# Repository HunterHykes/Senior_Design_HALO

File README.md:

# Senior_Design_HALO

This is the repository for the Hard Hat Ambient Liability Observer (H.A.L.O.) I assisted in developing for my senior design project at the University of Akron from Spring 2020 - Spring 2021.

<p align="center">

<p align="center">H.A.L.O. attached to a hard hat.</p>
</p>

<p align="center">

<p align="center">H.A.L.O. detached from a hard hat.</p>
</p>

## What the H.A.L.O. Does
This product is a hard hat attachment which utilizes six time-of-flight (ToF) sensors to detect hazards within a 1.5m radius from the wearer's head with a 150° field of view.

<p align="center">

<p align="center">H.A.L.O. Time-of-Flight Board.</p>
</p>

Dependent on the distance between the user and the hazard, some RGB LEDs placed near the brim of the hard hat will turn on and change hue from yellow to red as objects approach. This enhances the awareness of the user of potential hazards.

<p align="center">

<p align="center">H.A.L.O. RGB LED Board.</p>
</p>

In the event that the user hits their head either from a collision from walking or perhaps from slipping and falling, an on-board accelerometer will detect the impact severity.

If this impact is determined to pose a concussion threat to the user, the accelerometer data is logged to a .csv file on a micro-SD card, which can then be used to assess health-related concerns.

## Images

<p align="center">

<p align="center">H.A.L.O. being worn by myself.</p>
</p>

<!---  --->
<!---  --->
<!---  --->
<!---  --->
<!---  --->

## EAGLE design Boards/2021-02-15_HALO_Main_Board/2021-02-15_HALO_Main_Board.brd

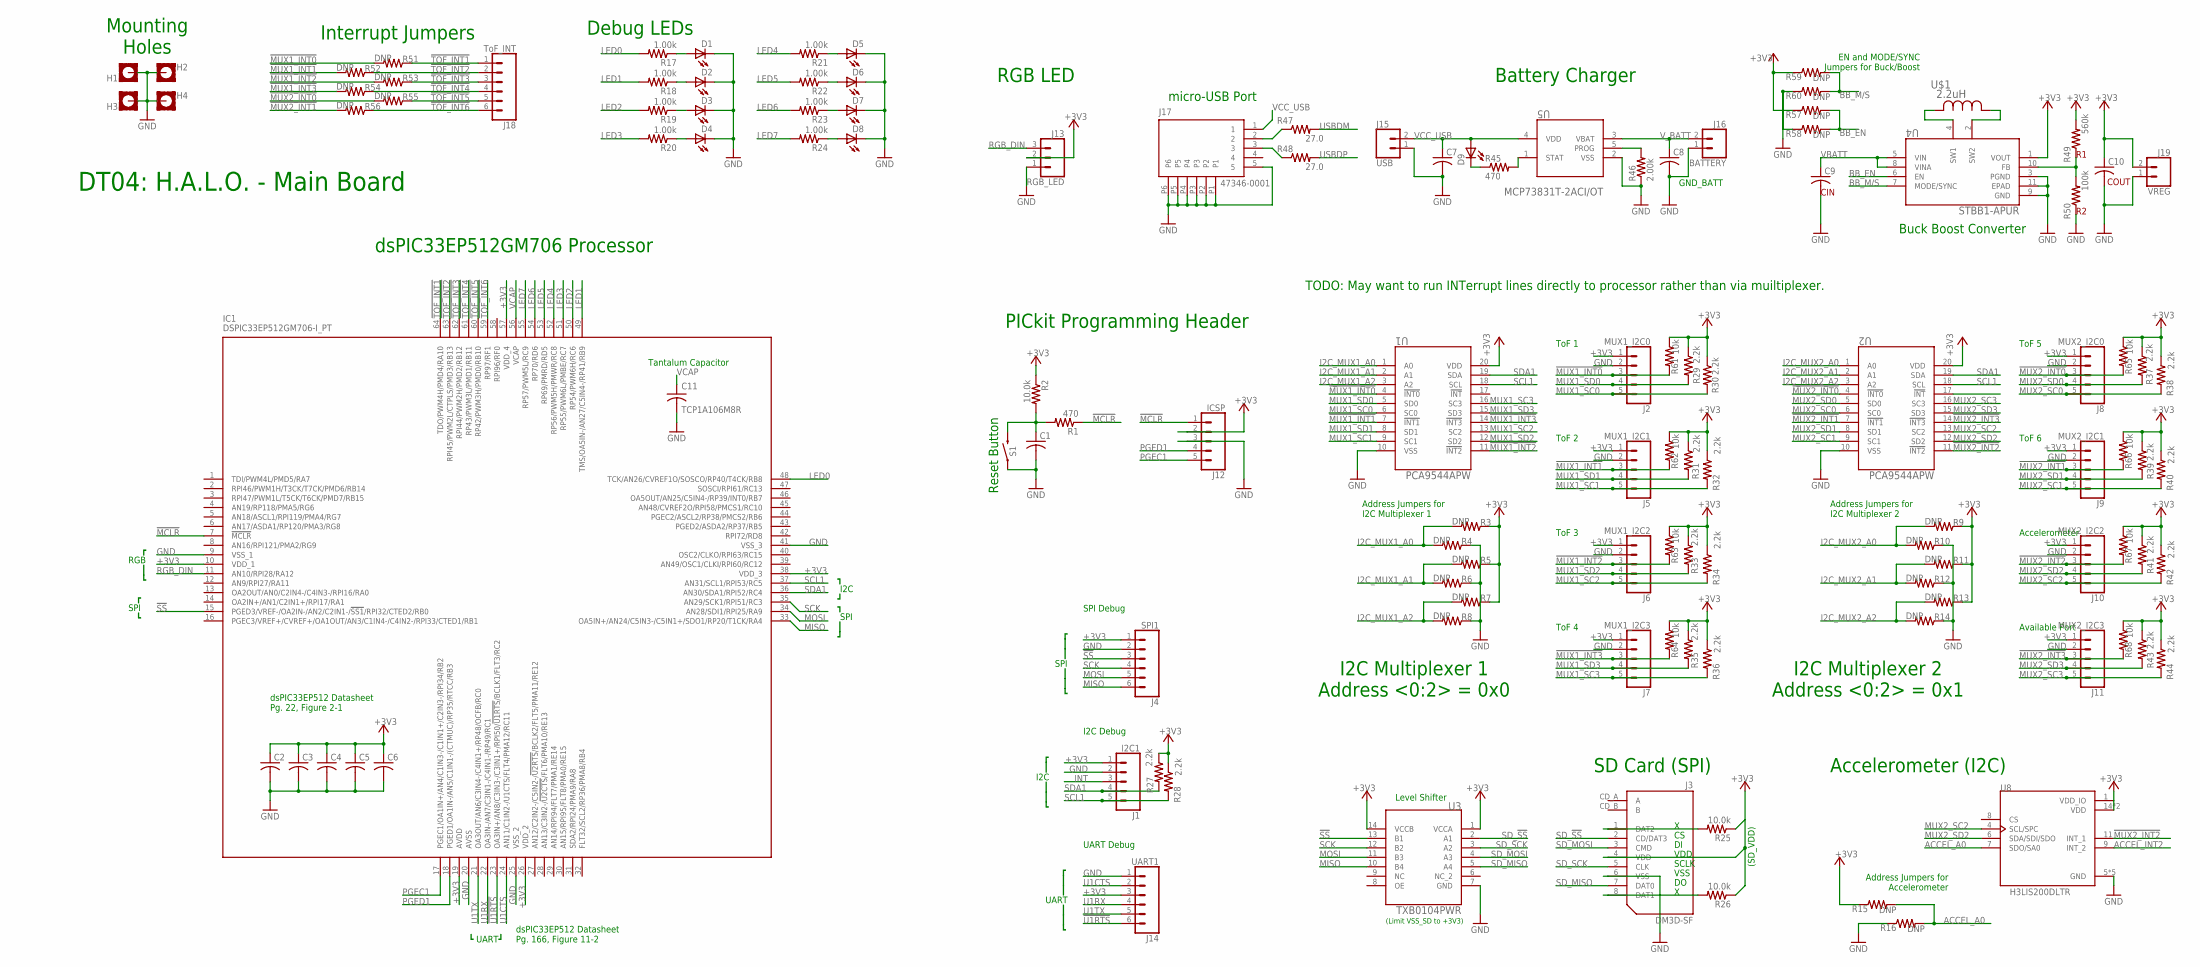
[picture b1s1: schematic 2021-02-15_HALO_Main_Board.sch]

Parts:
C1, C2, C3, C4, C5, C6: 0.1uF; C0805
C7, C8: 4.7uF; C0805
C9: 10uF; C0805
C10: 22uF; C0805
C11: TCP1A106M8R; TCP_ROM
D1, D2, D3, D4, D5, D6, D7, D8, D9: CHIP-LED0805
H1, H2, H3, H4: MOUNT-PAD-SQUARE3.0; 3,0-PAD-SQUARE
IC1: DSPIC33EP512GM706-I_PT; QFP50P1200X1200X120-64N
J1: I2C1; 1X05
J2: MUX1_I2C0; 1X05
J3: DM3D-SF; SD_CARD
J4: SPI1; 1X06
J5: MUX1_I2C1; 1X05
J6: MUX1_I2C2; 1X05
J7: MUX1_I2C3; 1X05
J8: MUX2_I2C0; 1X05
J9: MUX2_I2C1; 1X05
J10: MUX2_I2C2; 1X05
J11: MUX2_I2C3; 1X05
J12: ICSP; 1X05
J13: RGB_LED; 1X03_LOCK
J14: UART1; 1X06
J15: USB; 1X02
J16: BATTERY; 1X02
J17: 47346-0001; MICRO_USB; PARTNO AS-ITM-00021
J18: ToF_INT; 1X06
J19: VREG; 1X02
R1, R45: 470; R0805
R2, R25, R26: 10.0k; R0805
R3, R4, R5, R6, R7, R8, R9, R10, R11, R12, R13, R14, R15, R16, R51, R52, R53, R54, R55, R56, R57, R58, R59, R60: DNP; R0805
R17, R18, R19, R20, R21, R22, R23, R24: 1.00k; R0805
R27, R28, R29, R30, R31, R32, R33, R34, R35, R36, R37, R38, R39, R40, R41, R42, R43, R44: 2.2k; R0805
R46: 2.00k; R0805
R47, R48: 27.0; R0805
R49: 560k; R0805
R50: 100k; R0805
R61, R62, R63, R64, R65, R66, R67, R68: 10k; R0805
S1: SWITCH-MOMENTARY-2SMD-4; TACTILE_SWITCH_TALL
U1, U2: PCA9544APW; SOT360-1_NXP
U3: TXB0104PWR; PW14
U4: STBB1-APUR; SON_B1-APUR_STM
U5: MCP73831T-2ACI/OT; SOT-23-5_MC_MCH
U8: H3LIS200DLTR; PQFN50P300X300X100-16N
U$1: 2.2uH; IND_4028_TDK

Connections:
!MCLR: IC1.7 (!MCLR), J12.1, R1.1
!MUX1_INT0: J2.3, R51.2, R61.2, U1.4 (!INT0)
!MUX1_INT1: J5.3, R52.2, R62.2, U1.7 (!INT1)
!MUX1_INT2: J6.3, R53.2, R63.2, U1.11 (!INT2)
!MUX1_INT3: J7.3, R54.2, R64.2, U1.14 (!INT3)
!MUX2_INT0: J8.3, R55.2, R65.2, U2.4 (!INT0)
!MUX2_INT1: J9.3, R56.2, R66.2, U2.7 (!INT1)
!MUX2_INT2: J10.3, R67.2, U2.11 (!INT2), U8.11 (INT_1)
!MUX2_INT3: J11.3, R68.2, U2.14 (!INT3)
!SS: IC1.15 (PGED3/VREF-/OA2IN-/AN2/C2IN1-/!SS1!/RPI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), J4.3, U3.13 (B1)
!TOF_INT1: IC1.64 (TDO/PWM4H/PMD4/RA10), J18.1, R51.1
!TOF_INT2: IC1.63 (RPI45/PWM2L/CTPLS/PMD3/RB13), J18.2, R52.1
!TOF_INT3: IC1.62 (RPI44/PWM2H/PMD2/RB12), J18.3, R53.1
!TOF_INT4: IC1.61 (RP43/PWM3L/PMD1/RB11), J18.4, R54.1
!TOF_INT5: IC1.60 (RP42/PWM3H/PMD0/RB10), J18.5, R55.1
!TOF_INT6: IC1.59 (RP97/RF1), J18.6, R56.1
!U1RTS: IC1.23 (OA3IN+/AN8/C3IN3-/C3IN1+/RPI50/!U1RTS!/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), J14.6
+3V3: C2.1, C3.1, C4.1, C5.1, C6.1, C10.1, IC1.10 (VDD_1), IC1.19 (AVDD), IC1.26 (VDD_2), IC1.38 (VDD_3), IC1.57 (VDD_4), J1.1, J2.1, J3.4 (VDD), J4.1, J5.1, J6.1, J7.1, J8.1, J9.1, J10.1, J11.1, J12.2, J13.2, J14.3, J19.2, R2.1, R3.1, R5.1, R7.1, R9.1, R11.1, R13.1, R15.1, R25.1, R26.1, R27.1, R28.1, R29.1, R30.1, R31.1, R32.1, R33.1, R34.1, R35.1, R36.1, R37.1, R38.1, R39.1, R40.1, R41.1, R42.1, R43.1, R44.1, R49.2, R57.1, R59.1, R61.1, R62.1, R63.1, R64.1, R65.1, R66.1, R67.1, R68.1, U1.20 (VDD), U2.20 (VDD), U3.1 (VCCA), U3.14 (VCCB), U4.1 (VOUT), U8.1 (VDD_IO), U8.14 (VDD), U8.15 (VDD)
ACCEL_A0: R15.2, R16.2, U8.7 (SDO/SA0)
ACCEL_INT2: U8.9 (INT_2)
BB_EN: R57.2, R58.2, U4.6 (EN)
BB_M/S: R59.2, R60.2, U4.7 (MODE/SYNC)
GND: C1.2, C2.2, C3.2, C4.2, C5.2, C6.2, C7.2, C8.2, C9.2, C10.2, C11.2, D1.C, D2.C, D3.C, D4.C, D5.C, D6.C, D7.C, D8.C, H1.B3,0, H2.B3,0, H3.B3,0, H4.B3,0, IC1.9 (VSS_1), IC1.20 (AVSS), IC1.25 (VSS_2), IC1.41 (VSS_3), J1.2, J2.2, J3.6 (VSS), J4.2, J5.2, J6.2, J7.2, J8.2, J9.2, J10.2, J11.2, J12.3, J13.1, J14.1, J15.1, J16.1, J17.5, J17.P1, J17.P2, J17.P3, J17.P4, J17.P5, J17.P6, J19.1, R4.1, R6.1, R8.1, R10.1, R12.1, R14.1, R16.1, R46.1, R50.1, R58.1, R60.1, S1.A2 (1), U1.10 (VSS), U2.10 (VSS), U3.7 (GND), U4.3 (PGND), U4.9 (GND), U4.11 (EPAD), U5.2 (VSS), U8.5 (GND), U8.10 (GND), U8.12 (GND), U8.13 (GND), U8.16 (GND)
I2C_MUX1_A0: R3.2, R4.2, U1.1 (A0)
I2C_MUX1_A1: R5.2, R6.2, U1.2 (A1)
I2C_MUX1_A2: R7.2, R8.2, U1.3 (A2)
I2C_MUX2_A0: R9.2, R10.2, U2.1 (A0)
I2C_MUX2_A1: R11.2, R12.2, U2.2 (A1)
I2C_MUX2_A2: R13.2, R14.2, U2.3 (A2)
INT: J1.3
LED0: IC1.48 (TCK/AN26/CVREF1O/SOSCO/RP40/T4CK/RB8), R17.2
LED1: IC1.49 (TMS/OA5IN-/AN27/C5IN4-/RP41/RB9), R18.2
LED2: IC1.50 (RP54/PWM6H/RC6), R19.2
LED3: IC1.51 (RP55/PWM6L/PMBE/RC7), R20.2
LED4: IC1.52 (RP56/PWM5H/PMWR/RC8), R21.2
LED5: IC1.53 (RP69/PMRD/RD5), R22.2
LED6: IC1.54 (RP70/RD6), R23.2
LED7: IC1.55 (RP57/PWM5L/RC9), R24.2
MISO: IC1.33 (OA5IN+/AN24/C5IN3-/C5IN1+/SDO1/RP20/T1C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), J4.6, U3.10 (B4)
MOSI: IC1.34 (AN28/SDI1/RPI25/RA9), J4.5, U3.11 (B3)
MUX1_SC0: J2.5, R30.2, U1.6 (SC0)
MUX1_SC1: J5.5, R32.2, U1.9 (SC1)
MUX1_SC2: J6.5, R34.2, U1.13 (SC2)
MUX1_SC3: J7.5, R36.2, U1.16 (SC3)
MUX1_SD0: J2.4, R29.2, U1.5 (SD0)
MUX1_SD1: J5.4, R31.2, U1.8 (SD1)
MUX1_SD2: J6.4, R33.2, U1.12 (SD2)
MUX1_SD3: J7.4, R35.2, U1.15 (SD3)
MUX2_SC0: J8.5, R38.2, U2.6 (SC0)
MUX2_SC1: J9.5, R40.2, U2.9 (SC1)
MUX2_SC2: J10.5, R42.2, U2.13 (SC2), U8.4 (SCL/SPC)
MUX2_SC3: J11.5, R44.2, U2.16 (SC3)
MUX2_SD0: J8.4, R37.2, U2.5 (SD0)
MUX2_SD1: J9.4, R39.2, U2.8 (SD1)
MUX2_SD2: J10.4, R41.2, U2.12 (SD2), U8.6 (SDA/SDI/SDO)
MUX2_SD3: J11.4, R43.2, U2.15 (SD3)
unnamed: C1.1, R1.2, R2.2, S1.B2 (2)
unnamed: J3.8 (DAT1), R26.2
unnamed: J3.1 (DAT2), R25.2
unnamed: D1.A, R17.1
unnamed: J17.2, R47.1
unnamed: D2.A, R18.1
unnamed: D9.C, R45.1
unnamed: R49.1, R50.2, U4.10 (FB)
unnamed: D3.A, R19.1
unnamed: D4.A, R20.1
unnamed: D5.A, R21.1
unnamed: D6.A, R22.1
unnamed: D7.A, R23.1
unnamed: D8.A, R24.1
unnamed: R45.2, U5.1 (STAT)
unnamed: J17.3, R48.1
unnamed: U4.4 (SW1), U$1.2
unnamed: R46.2, U5.5 (PROG)
unnamed: U4.2 (SW2), U$1.1
PGEC1: IC1.17 (PGEC1/OA1IN+/AN4/C1IN3-/C1IN1+/C2IN3-/R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), J12.5
PGED1: IC1.18 (PGED1/OA1IN-/AN5/C1IN1-/(CTMUC)/RP35/RT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), J12.4
RGB_DIN: IC1.11 (AN10/RPI28/RA12), J13.3
SCK: IC1.35 (AN29/SCK1/RPI51/RC3), J4.4, U3.12 (B2)
SCL1: IC1.37 (AN31/SCL1/RPI53/RC5), J1.5, R28.2, U1.18 (SCL), U2.18 (SCL)
SDA1: IC1.36 (AN30/SDA1/RPI52/RC4), J1.4, R27.2, U1.19 (SDA), U2.19 (SDA)
SD_!SS: J3.2 (CD/DAT3), U3.2 (A1)
SD_MISO: J3.7 (DAT0), U3.5 (A4)
SD_MOSI: J3.3 (CMD), U3.4 (A3)
SD_SCK: J3.5 (CLK), U3.3 (A2)
U1CTS: IC1.24 (AN11/C1IN2-/U1CTS/FLT4/PMA12/RC11), J14.2
U1RX: IC1.22 (OA3IN-/AN7/C3IN1-/C4IN1-/RP49/RC1), J14.4
U1TX: IC1.21 (OA3OUT/AN6/C3IN4-/C4IN1+/RP48/OCFB/RC0), J14.5
USBDM: R47.2
USBDP: R48.2
VBATT: C9.1, U4.5 (VIN), U4.8 (VINA)
VCAP: C11.1, IC1.56 (VCAP)
VCC_USB: C7.1, D9.A, J15.2, J17.1, U5.4 (VDD)
V_BATT: C8.1, J16.2, U5.3 (VBAT)

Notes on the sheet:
┓ SPI ┃ ┛
┓ I2C ┛
Reset Button
VDD
SCLK
VSS
SD Card (SPI)
Address Jumpers for I2C Multiplexer 1
Address Jumpers for I2C Multiplexer 2
I2C Debug
SPI Debug
I2C Multiplexer 1 Address <0:2> = 0x0
I2C Multiplexer 2 Address <0:2> = 0x1
ToF 1
ToF 2
ToF 3
ToF 4
ToF 5
ToF 6
Accelerometer
Available Port
TODO: May want to run INTerrupt lines directly to processor rather than via muiltiplexer.
DT04: H.A.L.O. - Main Board
dsPIC33EP512 Datasheet Pg. 22, Figure 2-1
PICkit Programming Header
Debug LEDs
dsPIC33EP512 Datasheet Pg. 166, Figure 11-2
┗ UART┛
Level Shifter
(Limit VSS_SD to +3V3)
(SD_VDD)
RGB LED
Battery Charger
Buck Boost Converter
GND_BATT
Accelerometer (I2C)
Address Jumpers for Accelerometer
UART Debug
┏ ┃ I2C ┃ ┃ ┗
┏ ┃ ┃ SPI ┃ ┃ ┗

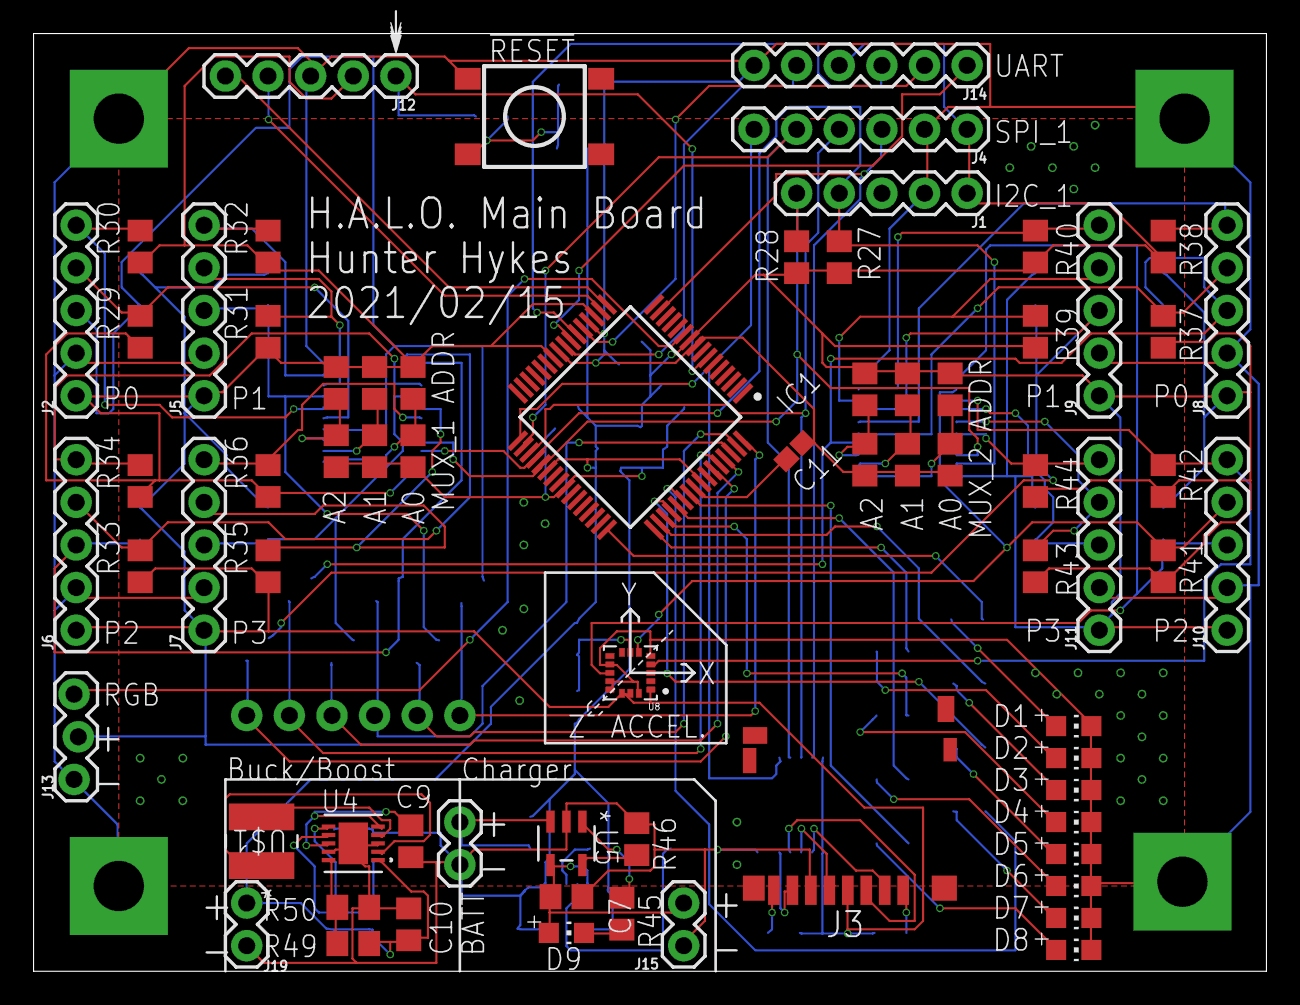
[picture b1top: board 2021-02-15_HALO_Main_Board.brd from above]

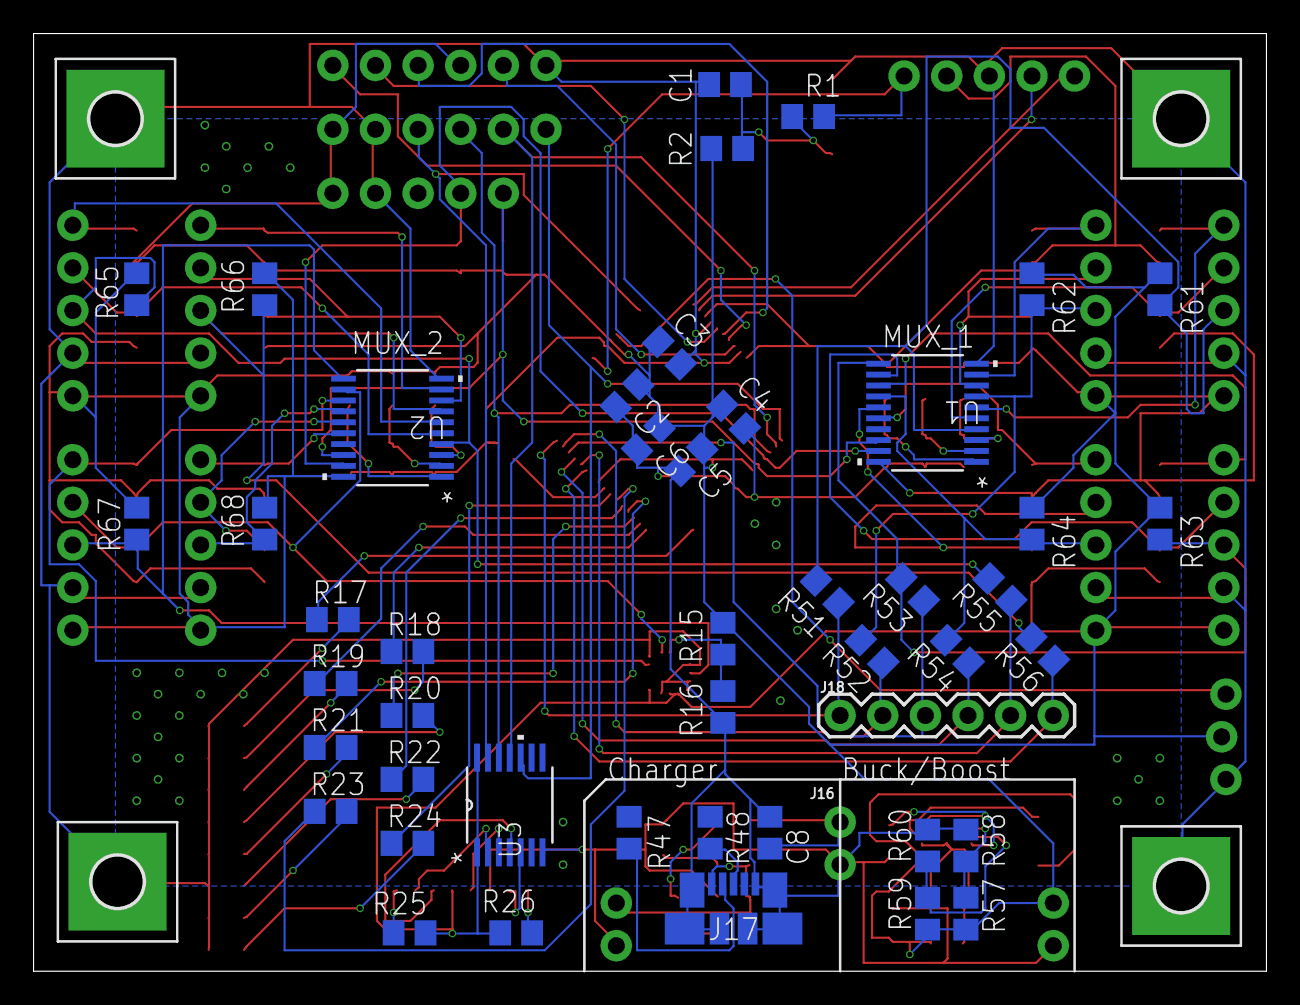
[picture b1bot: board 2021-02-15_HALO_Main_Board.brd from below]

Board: 2 copper layers, 73.5 x 55.9 mm, 120 parts (50 on the bottom side), 90 nets.

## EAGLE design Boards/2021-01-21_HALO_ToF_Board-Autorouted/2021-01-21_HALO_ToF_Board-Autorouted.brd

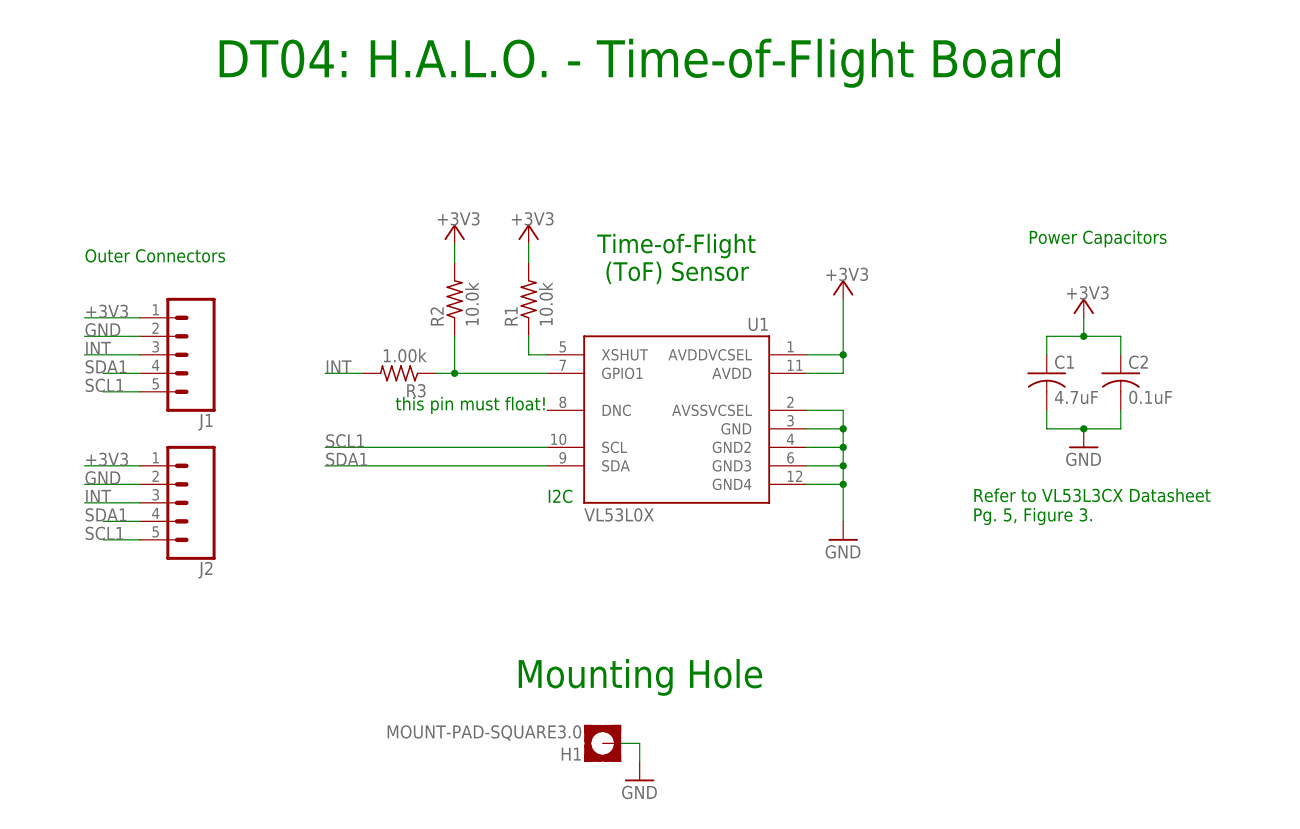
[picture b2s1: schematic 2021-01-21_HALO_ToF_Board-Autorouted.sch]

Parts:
C1: 4.7uF; C0805
C2: 0.1uF; C0805
H1: MOUNT-PAD-SQUARE3.0; 3,0-PAD-SQUARE
J1, J2: CONN_05; 1X05
R1, R2: 10.0k; R0805
R3: 1.00k; R0805
U1: VL53L0X

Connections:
+3V3: C1.1, C2.1, J1.1, J2.1, R1.2, R2.2, U1.1 (AVDDVCSEL), U1.11 (AVDD)
GND: C1.2, C2.2, H1.B3,0, J1.2, J2.2, U1.2 (AVSSVCSEL), U1.3 (GND), U1.4 (GND2), U1.6 (GND3), U1.12 (GND4)
INT: J1.3, J2.3, R3.2
unnamed: R1.1, U1.5 (XSHUT)
unnamed: R2.1, R3.1, U1.7 (GPIO1)
SCL1: J1.5, J2.5, U1.10 (SCL)
SDA1: J1.4, J2.4, U1.9 (SDA)

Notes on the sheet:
Outer Connectors
Refer to VL53L3CX Datasheet Pg. 5, Figure 3.
Power Capacitors
Time-of-Flight (ToF) Sensor
I2C
this pin must float!
DT04: H.A.L.O. - Time-of-Flight Board
Mounting Hole

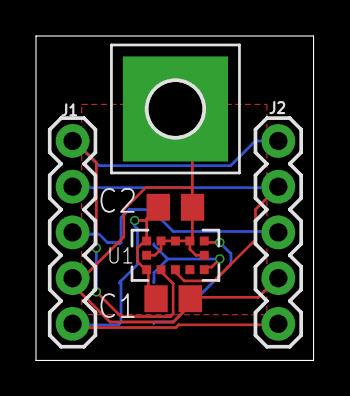
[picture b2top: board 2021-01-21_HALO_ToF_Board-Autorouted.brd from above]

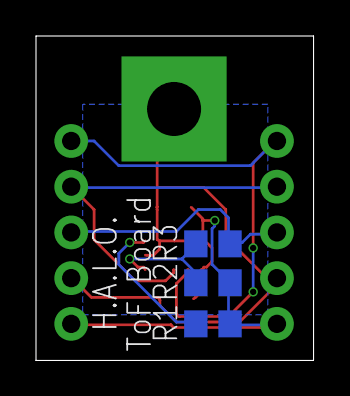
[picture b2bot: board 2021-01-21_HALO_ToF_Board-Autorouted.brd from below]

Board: 2 copper layers, 15.4 x 18.0 mm, 9 parts (3 on the bottom side), 7 nets.

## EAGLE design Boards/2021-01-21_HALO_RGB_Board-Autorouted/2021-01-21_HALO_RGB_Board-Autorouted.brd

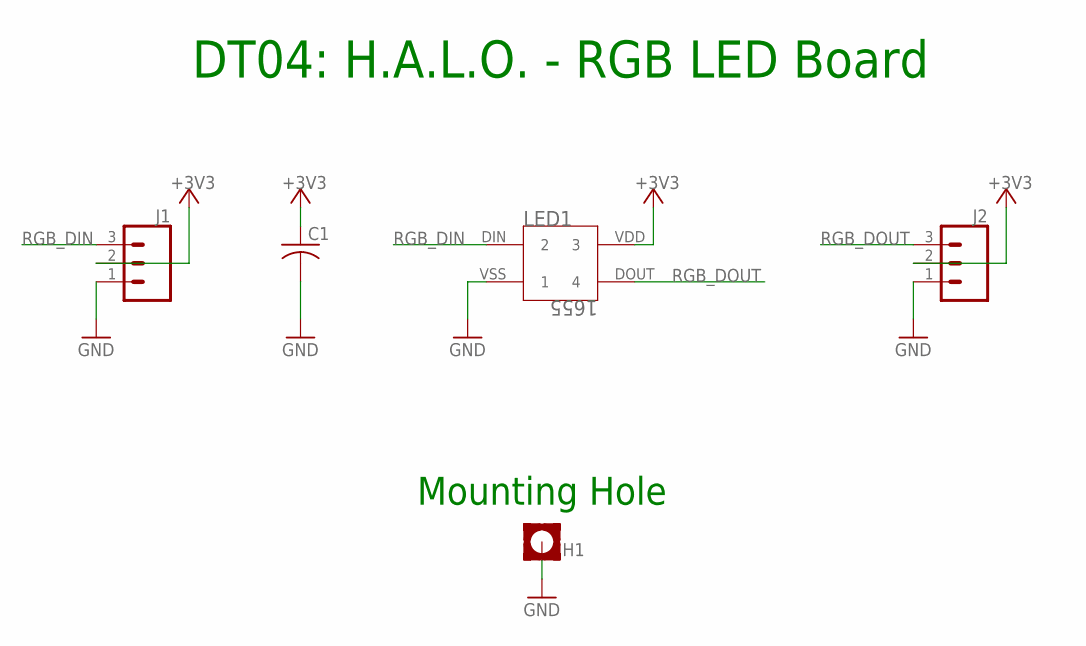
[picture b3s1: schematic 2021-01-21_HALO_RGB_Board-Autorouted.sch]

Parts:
C1: 1uF; C0805
H1: MOUNT-PAD-SQUARE3.0; 3,0-PAD-SQUARE
J1, J2: CONN_03LOCK; 1X03_LOCK
LED1: 1655; LED_1655_ADA

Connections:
+3V3: C1.1, J1.2, J2.2, LED1.VDD (3)
GND: C1.2, H1.B3,0, J1.1, J2.1, LED1.VSS (1)
RGB_DIN: J1.3, LED1.DIN (2)
RGB_DOUT: J2.3, LED1.DOUT (4)

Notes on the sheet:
DT04: H.A.L.O. - RGB LED Board
Mounting Hole

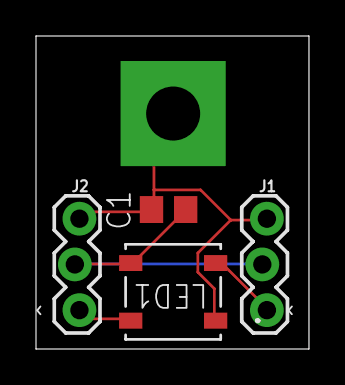
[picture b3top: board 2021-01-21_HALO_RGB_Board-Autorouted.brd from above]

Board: 2 copper layers, 15.2 x 17.4 mm, 5 parts (1 on the bottom side), 4 nets.

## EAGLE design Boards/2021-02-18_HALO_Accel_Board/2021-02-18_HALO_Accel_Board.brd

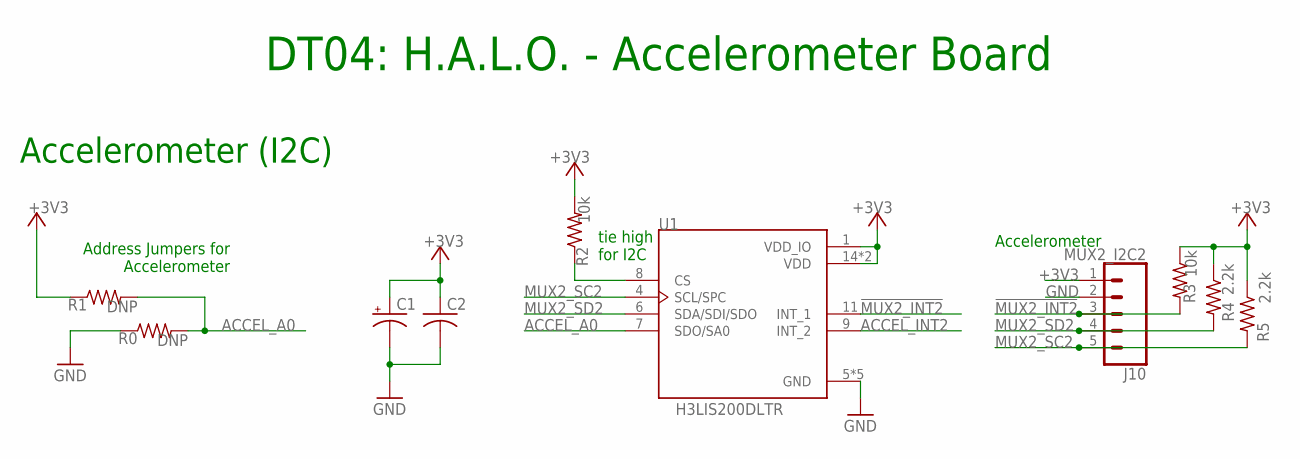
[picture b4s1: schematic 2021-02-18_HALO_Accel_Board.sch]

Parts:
C1: 10uF; EIA3216
C2: 0.1uF; C0805
J10: MUX2_I2C2; 1X05
R0, R1: DNP; R0805
R2, R3: 10k; R0805
R4, R5: 2.2k; R0805
U1: H3LIS200DLTR; PQFN50P300X300X100-16N

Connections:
!MUX2_INT2: J10.3, R3.2, U1.11 (INT_1)
+3V3: C1.+, C2.1, J10.1, R1.1, R2.2, R3.1, R4.1, R5.1, U1.1 (VDD_IO), U1.14 (VDD), U1.15 (VDD)
ACCEL_A0: R0.2, R1.2, U1.7 (SDO/SA0)
ACCEL_INT2: U1.9 (INT_2)
GND: C1.-, C2.2, J10.2, R0.1, U1.5 (GND), U1.10 (GND), U1.12 (GND), U1.13 (GND), U1.16 (GND)
MUX2_SC2: J10.5, R5.2, U1.4 (SCL/SPC)
MUX2_SD2: J10.4, R4.2, U1.6 (SDA/SDI/SDO)
unnamed: R2.1, U1.8 (CS)

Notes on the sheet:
Accelerometer
DT04: H.A.L.O. - Accelerometer Board
Accelerometer (I2C)
Address Jumpers for Accelerometer
tie high for I2C

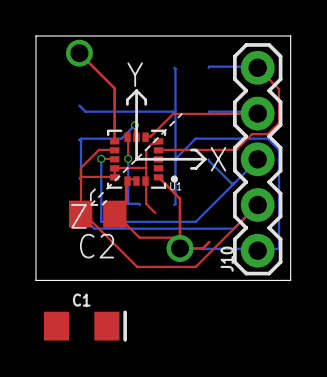
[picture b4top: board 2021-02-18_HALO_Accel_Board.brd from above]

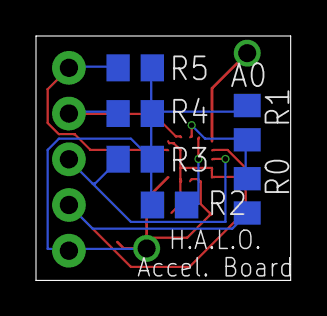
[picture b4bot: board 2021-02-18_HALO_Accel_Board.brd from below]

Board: 2 copper layers, 14.1 x 13.6 mm, 10 parts (6 on the bottom side), 7 nets.

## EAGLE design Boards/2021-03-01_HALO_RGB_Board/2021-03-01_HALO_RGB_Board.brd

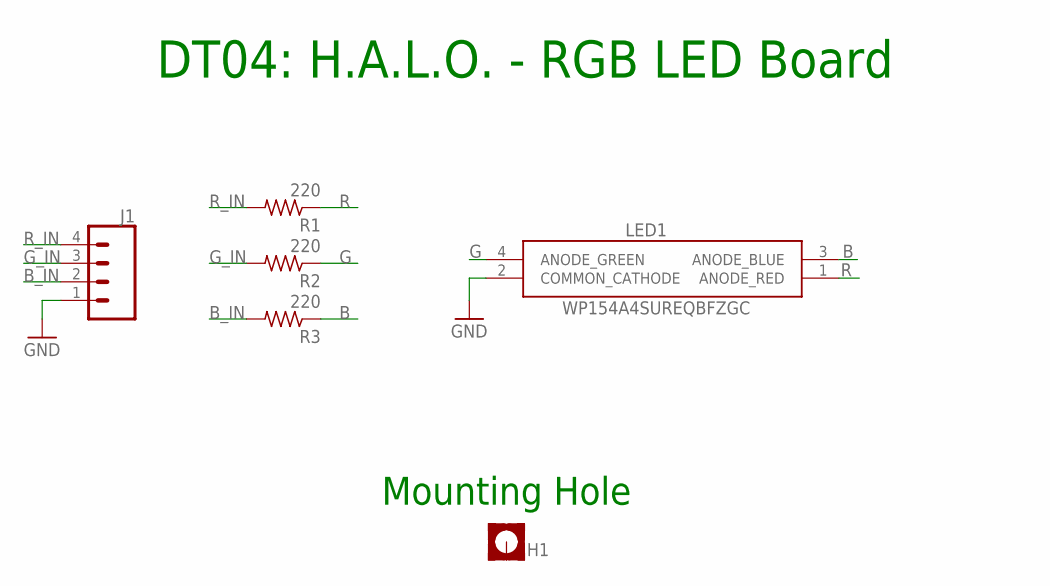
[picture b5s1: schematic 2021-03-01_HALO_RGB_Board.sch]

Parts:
H1: MOUNT-PAD-SQUARE3.0; 3,0-PAD-SQUARE
J1: CONN_04; 1X04
LED1: WP154A4SUREQBFZGC; L-154A4SUREQBFZGEC
R1, R2, R3: 220; R0805

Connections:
B: LED1.3 (ANODE_BLUE), R3.1
B_IN: J1.2, R3.2
G: LED1.4 (ANODE_GREEN), R2.1
GND: J1.1, LED1.2 (COMMON_CATHODE)
G_IN: J1.3, R2.2
R: LED1.1 (ANODE_RED), R1.1
R_IN: J1.4, R1.2

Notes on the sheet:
DT04: H.A.L.O. - RGB LED Board
Mounting Hole

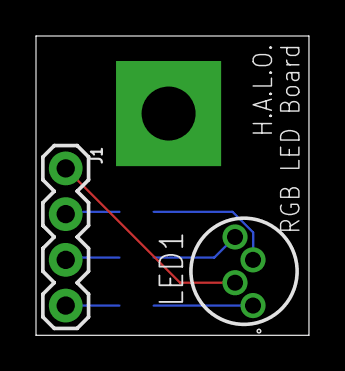
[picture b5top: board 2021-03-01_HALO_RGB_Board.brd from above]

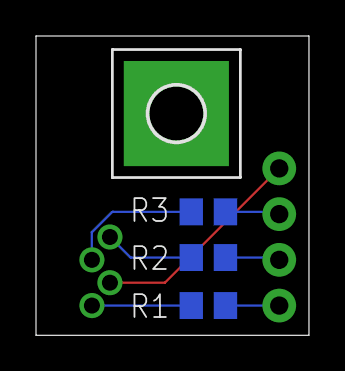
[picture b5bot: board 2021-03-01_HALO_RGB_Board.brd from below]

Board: 2 copper layers, 15.2 x 16.6 mm, 6 parts (4 on the bottom side), 7 nets.

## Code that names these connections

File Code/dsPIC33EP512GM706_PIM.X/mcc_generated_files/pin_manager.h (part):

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*/
/**
  @Summary
    Sets the GPIO pin, RA10, high using LATA10.

  @Description
    Sets the GPIO pin, RA10, high using LATA10.

  @Preconditions
    The RA10 must be set to an output.
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#define ToF_INT1_SetHigh()          (_LATA10 = 1)
/**
  @Summary
    Sets the GPIO pin, RA10, low using LATA10.

  @Description
    Sets the GPIO pin, RA10, low using LATA10.

  @Preconditions
    The RA10 must be set to an output.
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#define ToF_INT1_SetLow()           (_LATA10 = 0)
/**
  @Summary
    Toggles the GPIO pin, RA10, using LATA10.

  @Description
    Toggles the GPIO pin, RA10, using LATA10.

  @Preconditions
    The RA10 must be set to an output.
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#define ToF_INT1_Toggle()           (_LATA10 ^= 1)
/**
  @Summary
    Reads the value of the GPIO pin, RA10.

  @Description
    Reads the value of the GPIO pin, RA10.

  @Preconditions
    None.
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    </code>

*/
#define ToF_INT1_GetValue()         _RA10
/**
  @Summary
    Configures the GPIO pin, RA10, as an input.

  @Description
    Configures the GPIO pin, RA10, as an input.

  @Preconditions
    None.
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#define ToF_INT1_SetDigitalInput()  (_TRISA10 = 1)
/**
  @Summary
    Configures the GPIO pin, RA10, as an output.

  @Description
    Configures the GPIO pin, RA10, as an output.

  @Preconditions
    None.
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#define ToF_INT1_SetDigitalOutput() (_TRISA10 = 0)
/**
  @Summary
    Sets the GPIO pin, RA4, high using LATA4.

  @Description
    Sets the GPIO pin, RA4, high using LATA4.

  @Preconditions
    The RA4 must be set to an output.
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#define SDO1_SetHigh()          (_LATA4 = 1)
/**
  @Summary
    Sets the GPIO pin, RA4, low using LATA4.

  @Description
    Sets the GPIO pin, RA4, low using LATA4.

  @Preconditions
    The RA4 must be set to an output.
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#define SDO1_SetLow()           (_LATA4 = 0)
/**
  @Summary
    Toggles the GPIO pin, RA4, using LATA4.

  @Description
    Toggles the GPIO pin, RA4, using LATA4.

  @Preconditions
    The RA4 must be set to an output.
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#define SDO1_Toggle()           (_LATA4 ^= 1)
/**
  @Summary
    Reads the value of the GPIO pin, RA4.

  @Description
    Reads the value of the GPIO pin, RA4.

  @Preconditions
    None.
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    </code>

*/
#define SDO1_GetValue()         _RA4
/**
  @Summary
    Configures the GPIO pin, RA4, as an input.

  @Description
    Configures the GPIO pin, RA4, as an input.

  @Preconditions
    None.
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#define SDO1_SetDigitalInput()  (_TRISA4 = 1)
/**
  @Summary
    Configures the GPIO pin, RA4, as an output.

  @Description
    Configures the GPIO pin, RA4, as an output.

  @Preconditions
    None.
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#define SDO1_SetDigitalOutput() (_TRISA4 = 0)
/**
  @Summary
    Sets the GPIO pin, RA9, high using LATA9.

  @Description
    Sets the GPIO pin, RA9, high using LATA9.

  @Preconditions
    The RA9 must be set to an output.
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#define SDI1_SetHigh()          (_LATA9 = 1)
/**
  @Summary
    Sets the GPIO pin, RA9, low using LATA9.

  @Description
    Sets the GPIO pin, RA9, low using LATA9.

  @Preconditions
    The RA9 must be set to an output.
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#define SDI1_SetLow()           (_LATA9 = 0)
/**
  @Summary
    Toggles the GPIO pin, RA9, using LATA9.

  @Description
    Toggles the GPIO pin, RA9, using LATA9.

  @Preconditions
    The RA9 must be set to an output.
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#define SDI1_Toggle()           (_LATA9 ^= 1)
/**
  @Summary
    Reads the value of the GPIO pin, RA9.

  @Description
    Reads the value of the GPIO pin, RA9.

  @Preconditions
    None.
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    </code>

*/
#define SDI1_GetValue()         _RA9
/**
  @Summary
    Configures the GPIO pin, RA9, as an input.

  @Description
    Configures the GPIO pin, RA9, as an input.

  @Preconditions
    None.
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#define SDI1_SetDigitalInput()  (_TRISA9 = 1)
/**
  @Summary
    Configures the GPIO pin, RA9, as an output.

  @Description
    Configures the GPIO pin, RA9, as an output.

  @Preconditions
    None.
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#define SDI1_SetDigitalOutput() (_TRISA9 = 0)
/**
  @Summary
    Sets the GPIO pin, RB0, high using LATB0.

  @Description
    Sets the GPIO pin, RB0, high using LATB0.

  @Preconditions
    The RB0 must be set to an output.
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#define SDCard_CS_SetHigh()          (_LATB0 = 1)
/**
  @Summary
    Sets the GPIO pin, RB0, low using LATB0.

  @Description
    Sets the GPIO pin, RB0, low using LATB0.

  @Preconditions
    The RB0 must be set to an output.
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#define SDCard_CS_SetLow()           (_LATB0 = 0)
/**
  @Summary
    Toggles the GPIO pin, RB0, using LATB0.

  @Description
    Toggles the GPIO pin, RB0, using LATB0.

  @Preconditions
    The RB0 must be set to an output.
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#define SDCard_CS_Toggle()           (_LATB0 ^= 1)
/**
  @Summary
    Reads the value of the GPIO pin, RB0.

  @Description
    Reads the value of the GPIO pin, RB0.

  @Preconditions
    None.
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    </code>

*/
#define SDCard_CS_GetValue()         _RB0
/**
  @Summary
    Configures the GPIO pin, RB0, as an input.

  @Description
    Configures the GPIO pin, RB0, as an input.

  @Preconditions
    None.
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#define SDCard_CS_SetDigitalInput()  (_TRISB0 = 1)
/**
  @Summary
    Configures the GPIO pin, RB0, as an output.

  @Description
    Configures the GPIO pin, RB0, as an output.

  @Preconditions
    None.
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#define SDCard_CS_SetDigitalOutput() (_TRISB0 = 0)
/**
  @Summary
    Sets the GPIO pin, RB10, high using LATB10.

  @Description
    Sets the GPIO pin, RB10, high using LATB10.

  @Preconditions
    The RB10 must be set to an output.
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#define ToF_INT5_SetHigh()          (_LATB10 = 1)
/**
  @Summary
    Sets the GPIO pin, RB10, low using LATB10.

  @Description
    Sets the GPIO pin, RB10, low using LATB10.

  @Preconditions
    The RB10 must be set to an output.
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#define ToF_INT5_SetLow()           (_LATB10 = 0)
/**
  @Summary
    Toggles the GPIO pin, RB10, using LATB10.

  @Description
    Toggles the GPIO pin, RB10, using LATB10.

  @Preconditions
    The RB10 must be set to an output.
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#define ToF_INT5_Toggle()           (_LATB10 ^= 1)
/**
  @Summary
    Reads the value of the GPIO pin, RB10.

  @Description
    Reads the value of the GPIO pin, RB10.

  @Preconditions
    None.
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    </code>

*/
#define ToF_INT5_GetValue()         _RB10
/**
  @Summary
    Configures the GPIO pin, RB10, as an input.

  @Description
    Configures the GPIO pin, RB10, as an input.

  @Preconditions
    None.
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#define ToF_INT5_SetDigitalInput()  (_TRISB10 = 1)
/**
  @Summary
    Configures the GPIO pin, RB10, as an output.

  @Description
    Configures the GPIO pin, RB10, as an output.

  @Preconditions
    None.
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#define ToF_INT5_SetDigitalOutput() (_TRISB10 = 0)
/**
  @Summary
    Sets the GPIO pin, RB11, high using LATB11.

  @Description
    Sets the GPIO pin, RB11, high using LATB11.

  @Preconditions
    The RB11 must be set to an output.
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#define ToF_INT4_SetHigh()          (_LATB11 = 1)
/**
  @Summary
    Sets the GPIO pin, RB11, low using LATB11.

  @Description
    Sets the GPIO pin, RB11, low using LATB11.

  @Preconditions
    The RB11 must be set to an output.
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#define ToF_INT4_SetLow()           (_LATB11 = 0)
/**
  @Summary
    Toggles the GPIO pin, RB11, using LATB11.

  @Description
    Toggles the GPIO pin, RB11, using LATB11.

  @Preconditions
    The RB11 must be set to an output.
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#define ToF_INT4_Toggle()           (_LATB11 ^= 1)
/**
  @Summary
    Reads the value of the GPIO pin, RB11.

  @Description
    Reads the value of the GPIO pin, RB11.

  @Preconditions
    None.
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    </code>

*/
#define ToF_INT4_GetValue()         _RB11
/**
  @Summary
    Configures the GPIO pin, RB11, as an input.

  @Description
    Configures the GPIO pin, RB11, as an input.

  @Preconditions
    None.
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#define ToF_INT4_SetDigitalInput()  (_TRISB11 = 1)
/**
  @Summary
    Configures the GPIO pin, RB11, as an output.

  @Description
    Configures the GPIO pin, RB11, as an output.

  @Preconditions
    None.
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#define ToF_INT4_SetDigitalOutput() (_TRISB11 = 0)
/**
  @Summary
    Sets the GPIO pin, RB12, high using LATB12.

  @Description
    Sets the GPIO pin, RB12, high using LATB12.

  @Preconditions
    The RB12 must be set to an output.
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#define ToF_INT3_SetHigh()          (_LATB12 = 1)
/**
  @Summary
    Sets the GPIO pin, RB12, low using LATB12.

  @Description
    Sets the GPIO pin, RB12, low using LATB12.

  @Preconditions
    The RB12 must be set to an output.
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#define ToF_INT3_SetLow()           (_LATB12 = 0)
/**
  @Summary
    Toggles the GPIO pin, RB12, using LATB12.

  @Description
    Toggles the GPIO pin, RB12, using LATB12.

  @Preconditions
    The RB12 must be set to an output.
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#define ToF_INT3_Toggle()           (_LATB12 ^= 1)
/**
  @Summary
    Reads the value of the GPIO pin, RB12.

  @Description
    Reads the value of the GPIO pin, RB12.

  @Preconditions
    None.
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    </code>

*/
#define ToF_INT3_GetValue()         _RB12
/**
  @Summary
    Configures the GPIO pin, RB12, as an input.

  @Description
    Configures the GPIO pin, RB12, as an input.

  @Preconditions
    None.
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#define ToF_INT3_SetDigitalInput()  (_TRISB12 = 1)
/**
  @Summary
    Configures the GPIO pin, RB12, as an output.

  @Description
    Configures the GPIO pin, RB12, as an output.

  @Preconditions
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
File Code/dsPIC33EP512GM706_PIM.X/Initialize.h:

/* Microchip Technology Inc. and its subsidiaries.  You may use this software 
 * and any derivatives exclusively with Microchip products. 
 * 
 * THIS SOFTWARE IS SUPPLIED BY MICROCHIP "AS IS".  NO WARRANTIES, WHETHER 
 * EXPRESS, IMPLIED OR STATUTORY, APPLY TO THIS SOFTWARE, INCLUDING ANY IMPLIED 
 * WARRANTIES OF NON-INFRINGEMENT, MERCHANTABILITY, AND FITNESS FOR A 
 * PARTICULAR PURPOSE, OR ITS INTERACTION WITH MICROCHIP PRODUCTS, COMBINATION 
 * WITH ANY OTHER PRODUCTS, OR USE IN ANY APPLICATION. 
 *
 * IN NO EVENT WILL MICROCHIP BE LIABLE FOR ANY INDIRECT, SPECIAL, PUNITIVE, 
 * INCIDENTAL OR CONSEQUENTIAL LOSS, DAMAGE, COST OR EXPENSE OF ANY KIND 
 * WHATSOEVER RELATED TO THE SOFTWARE, HOWEVER CAUSED, EVEN IF MICROCHIP HAS 
 * BEEN ADVISED OF THE POSSIBILITY OR THE DAMAGES ARE FORESEEABLE.  TO THE 
 * FULLEST EXTENT ALLOWED BY LAW, MICROCHIP'S TOTAL LIABILITY ON ALL CLAIMS 
 * IN ANY WAY RELATED TO THIS SOFTWARE WILL NOT EXCEED THE AMOUNT OF FEES, IF 
 * ANY, THAT YOU HAVE PAID DIRECTLY TO MICROCHIP FOR THIS SOFTWARE.
 *
 * MICROCHIP PROVIDES THIS SOFTWARE CONDITIONALLY UPON YOUR ACCEPTANCE OF THESE 
 * TERMS. 
 */

/* 
 * File:   
 * Author: 
 * Comments:
 * Revision history: 
 */

#ifndef INITIALIZE_H
#define	INITIALIZE_H

#include <xc.h> // include processor files - each processor file is guarded.  

#define ON 1
#define OFF 0

#define INPUT 1
#define OUTPUT 0

/* * * * * * * * * * * * On-Board LED Definitions * * * * * * * * * * * */
#define LED1 LATBbits.LATB8
#define LED2 LATBbits.LATB9
#define LED3 LATCbits.LATC6
#define LED4 LATCbits.LATC7
#define LED5 LATCbits.LATC8
#define LED6 LATDbits.LATD5
#define LED7 LATDbits.LATD6
#define LED8 LATCbits.LATC9

#define pinModeLED1 TRISBbits.TRISB8
#define pinModeLED2 TRISBbits.TRISB9
#define pinModeLED3 TRISCbits.TRISC6
#define pinModeLED4 TRISCbits.TRISC7
#define pinModeLED5 TRISCbits.TRISC8
#define pinModeLED6 TRISDbits.TRISD5
#define pinModeLED7 TRISDbits.TRISD6
#define pinModeLED8 TRISCbits.TRISC9
/* * * * * * * * * * * * * * * * * * * * * * * * * * * * * * * * * * * */

/* * * * * * * * * * * * ToF Interrupt Definitions * * * * * * * * * * * */
//#define ToF_INT_1 PORTAbits.RA10
//#define ToF_INT_2 PORTBbits.RB13
//#define ToF_INT_3 PORTBbits.RB12
//#define ToF_INT_4 PORTBbits.RB11
//#define ToF_INT_5 PORTBbits.RB10
//#define ToF_INT_6 PORTFbits.RF1
//
//#define pinMode_ToF_INT_1 TRISAbits.TRISA10
//#define pinMode_ToF_INT_2 TRISBbits.TRISB13
//#define pinMode_ToF_INT_3 TRISBbits.TRISB12
//#define pinMode_ToF_INT_4 TRISBbits.TRISB11
//#define pinMode_ToF_INT_5 TRISBbits.TRISB10
//#define pinMode_ToF_INT_6 TRISFbits.TRISF1
/* * * * * * * * * * * * * * * * * * * * * * * * * * * * * * * * * * * */

//bool Initialize();
void Start_Initialization();
//switches the clock from the FRC to the external HS oscillator
void oscillator(void);
void timerOne(void);
void timerTwo(void);

void init_SPI();

#endif	/* XC_HEADER_TEMPLATE_H */

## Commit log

2021-03-18 Added accelerometer code
2021-03-29 Added RGB definitions. Tested micro-SD writes.
2021-04-03 Functioning ToF and RGB LED code.
2021-04-20 Upload of final code
2021-04-24 added images
2021-04-24 added images to README

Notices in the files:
Code/dsPIC33EP512GM706_PIM.X/mcc_generated_files/pin_manager.h:
(c) 2020 Microchip Technology Inc. and its subsidiaries. You may use this
parts and their libraries:
SparkFun-Connectors: Licensing: Creative Commons ShareAlike 4.0 International - https://creativecommons.org/licenses/by-sa/4.0
COPYRIGHT: Copyright (C) 2018 Accelerated Designs. All rights reserved
